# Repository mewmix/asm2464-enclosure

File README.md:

# ASM2464PD USB4 / M.2 2230 Development Enclosure

Open development project for a compact ASM2464PD + M.2 2230 USB4 enclosure with firmware-development access built into the board and enclosure.

The immediate goals are:

1. reproduce and then improve the public Leaves232 ASM2464PD 2230 reference design;
2. expose the ASM2464PD firmware UART cleanly;
3. provide safe direct SPI access to the external firmware flash for backup, programming, and recovery;
4. co-design the PCB and enclosure rather than treating the enclosure as an afterthought;
5. use an agent-driven KiCad workflow modeled on the public i2cjak Astra + KiStack + T3CAD demonstration;
6. validate as much of the digital/recovery path as possible in simulation before Rev-A hardware.

## Agent-driven workflow

The public i2cjak demonstration describes an Astra-Medium hardware-design loop using **KiStack** and **T3CAD**, a T3Code fork. The exact private prompt/transcript is not published, so this repository documents a reproducible workflow built from the public tools and their documented capabilities.

Start with [`WORKFLOW.md`](WORKFLOW.md). Agents working in this repository must also read [`AGENTS.md`](AGENTS.md) and [`PROJECT_PLAN.md`](PROJECT_PLAN.md).

## Reference design

Electrical/mechanical reference:

- https://github.com/Leaves232/2230-USB4-SSD-Enclosure-Design

Controller datasheet pointer and extracted debug pins:

- [`reference/datasheets/ASM2464PD.md`](reference/datasheets/ASM2464PD.md)

Known reference-board geometry already extracted from the public Gerber/PnP data:

- controller PCB: **22.039834 x 33.680400 mm**;
- ASM2464PD center: **(13.667257, 14.870481) mm** from the PCB lower-left datum;
- USB-C center: **(11.069980, 29.187267) mm**;
- M.2 connector center: **(11.023879, 4.697654) mm**.

## Firmware-development interface

The service interface is deliberately narrow:

- ASM UART TX/RX;
- ASM reset;
- direct external SPI flash CS#/CLK/DI/DO;
- GND and target-voltage sense.

See [`DEBUG_ACCESS_AGENT_INSTRUCTIONS.md`](DEBUG_ACCESS_AGENT_INSTRUCTIONS.md).

## Mechanical model

The current CadQuery fit model lives at:

```text
mechanical/rev-a/model.py
```

Build it with:

```bash
python -m venv .venv
source .venv/bin/activate
pip install -r mechanical/rev-a/requirements.txt
python mechanical/rev-a/model.py
```

Generated STEP/STL files belong under `mechanical/rev-a/build/` and are intentionally ignored until geometry is mature enough to publish as release artifacts.

## Integrated CAD / simulation milestone

The primary simulation target is now stock/reconstructed ASM behavior, pinned
to lifecycle commit `84c990c` with physical baseline `47aed2c`. The stock code
mode executes exact bounded helpers with boot ROM bypassed; full stock SPI
startup remains blocked. The 512 KiB stock flash profile is separate from the
2 MiB Rev-A design assumption. See [stock evidence and limits](validation/STOCK_GROUNDING.md).

The shared board configuration drives service access, SPI-isolation shunts,
flash envelope clearance and the virtual board. The secondary generic CPU
regression validates this project-owned diagnostic image's modeled UART/SPI,
brick and recovery behavior. It does not establish stock firmware or physical
silicon behavior. Existing CAD renders remain historical until regenerated.

```bash
python -m pip install -r simulation/requirements.txt
# Install SDCC using your platform package manager, then:
python scripts/validate_twin.py
```

See [validation outputs and limits](validation/README.md) and [the shared recovery design](hardware/rev-a/RECOVERY.md). STEP/STL and assembled/exploded PNGs are generated in `mechanical/rev-a/build/`. Geometry includes explicit provisional component envelopes, not a completed routed PCB.

**RTL remains blocked:** no Verilog/RTL sources exist at the inspected authoritative branch tip. `--require-rtl` makes that missing gate fail explicitly. No full dual-backend or fabrication-ready claim is made.

## Design gates before fabrication

Do not release Rev A for fabrication until:

- reference schematic/net tracing is complete;
- UART voltage is established;
- SPI flash voltage and exact part pinout are established;
- ASM SPI bus ownership under reset is proven or explicit isolation is designed;
- ERC/DRC pass with reviewed waivers only;
- USB4/PCIe routing rules are reviewed independently of generic DRC;
- debug connector and mating-cable keepouts are present in the mechanical model;
- ASM thermal path is modeled and does not depend on a printed-plastic lid for sustained operation;
- recovery simulation proves brick -> external flash recovery -> reboot -> UART confirmation.

## Source toolchain

- KiCad / `kicad-cli`
- KiStack: https://github.com/American-Embedded/KiStack
- T3CAD: https://github.com/i2cjak/T3CAD
- CadQuery
- Verilator + cocotb for digital board simulation
- ngspice/Xyce where circuit-level modeling is useful
- LiteNVMe as an optional open NVMe-host reference

## License / reference hygiene

Do not copy third-party source designs or datasheets into this repository unless their license permits redistribution. Keep source pointers, extracted facts, and our own derived design work separated and attributed.

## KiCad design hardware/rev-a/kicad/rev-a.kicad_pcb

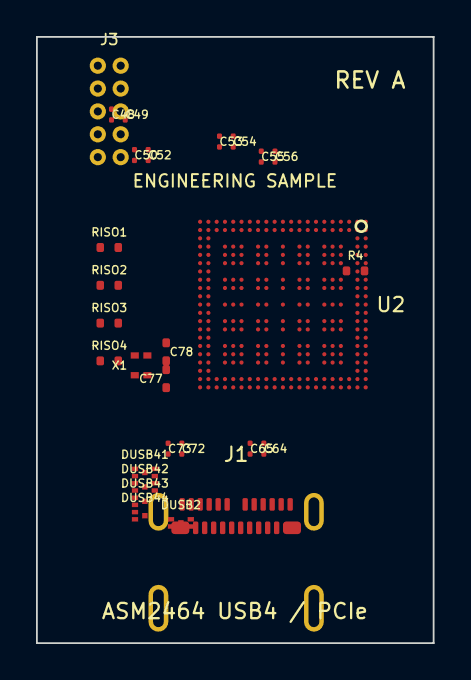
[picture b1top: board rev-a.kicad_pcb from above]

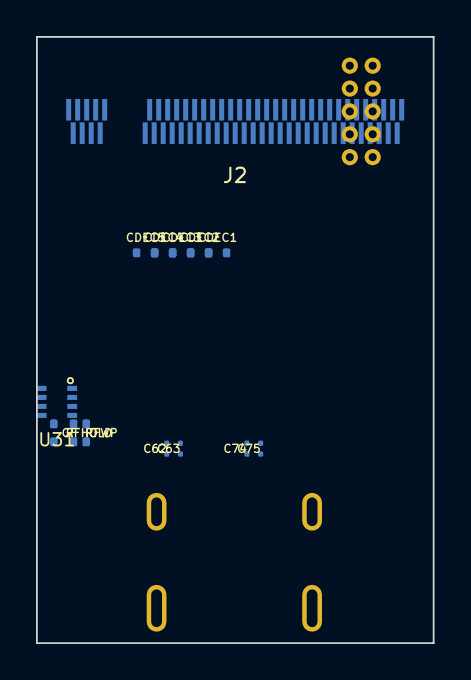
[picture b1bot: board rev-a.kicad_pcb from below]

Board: 2 copper layers, 22.0 x 33.7 mm, 42 parts (14 on the bottom side), 71 nets, no tracks yet.

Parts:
C48, C49, C50, C52, C53, C54, C55, C56, C64, C65, C74, C75: 220n; RevA_0201_2Pad
C62, C63, C72, C73: 330n; RevA_0201_2Pad
C77, C78: 30p; RevA_0402_2Pad
CDEC1, CDEC3, CDEC4, CDEC5: 100n; RevA_0402_2Pad
CDEC2: 2.2u; RevA_0402_2Pad
CF: 100n; RevA_0402_2Pad
DUSB2: ESD_2CH_SELECTION_PENDING; RevA_ESD2_SELECTION_PENDING_DUSB2
DUSB41: ESD_2CH_SELECTION_PENDING; RevA_ESD2_SELECTION_PENDING_DUSB41
DUSB42: ESD_2CH_SELECTION_PENDING; RevA_ESD2_SELECTION_PENDING_DUSB42
DUSB43: ESD_2CH_SELECTION_PENDING; RevA_ESD2_SELECTION_PENDING_DUSB43
DUSB44: ESD_2CH_SELECTION_PENDING; RevA_ESD2_SELECTION_PENDING_DUSB44
J1: 105450-0101; Molex_105450-0101
J2: APCI0113-P001A; LOTES_APCI0113-P001A_MKey_RECONSTRUCTED
J3: SERVICE_PROVISIONAL; RevA_Service_2x5_1.27_PROVISIONAL
R4: 12.1k; RevA_0402_2Pad
RFHOLD: 10k; RevA_0402_2Pad
RFWP: 10k; RevA_0402_2Pad
RISO1, RISO2, RISO3, RISO4: 0R_LINK; RevA_0402_2Pad
U2: ASM2464PD; ASM2464PD_BGA273_10x10_P0.46
U31: ZD25WQ16CEIGR; ZD25WQ16CEIGR_USON8_3x2_P0.5_RECONSTRUCTED
X1: 25MHz; RevA_Crystal_4P_1.6x1.2_X1

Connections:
+1V05: CDEC1.1, CDEC2.1, U2.D14, U2.D16, U2.E11, U2.E14, U2.E16, U2.F9, U2.F11, U2.F14, U2.F16, U2.H9, U2.H11, U2.H13, U2.H14, U2.H16, U2.J8, U2.J9, U2.J13, U2.J14, U2.J16, U2.J17, U2.J18, U2.J20, U2.J21, U2.K20, U2.K21, U2.L8, U2.L11, U2.L14, U2.N8, U2.N14, U2.P8, U2.P13, U2.P14, U2.T8, U2.T9, U2.T11, U2.T13, U2.T14, U2.U8, U2.U9
+1V8: CDEC3.1, U2.L6, U2.L16, U2.L17, U2.L18, U2.L20, U2.L21, U2.N6, U2.N16, U2.P6, U2.P16, U2.T6, U2.T16, U2.U6, U2.U11, U2.U13, U2.U14, U2.U16
+3V3: CDEC4.1, CF.1, J2.2, J2.4, J2.69, RFHOLD.2, RFWP.2, U2.D6, U2.D8, U2.D9, U2.D13, U2.E6, U2.E8, U2.E9, U2.E13, U2.F6, U2.F13, U2.H6, U31.8
+3V3A: CDEC5.1, U2.H5
ASM_REXT: R4.1, U2.AA3
ASM_RST_N: J3.5, U2.H1
ASM_SPI_CLK_CTRL: RISO2.1, U2.A5
ASM_SPI_CLK_FLASH: J3.7, RISO2.2, U31.6
ASM_SPI_CS_N_CTRL: RISO1.1, U2.A2
ASM_SPI_CS_N_FLASH: J3.6, RISO1.2, U31.1
ASM_SPI_DI_CTRL: RISO3.1, U2.A4
ASM_SPI_DI_FLASH: J3.8, RISO3.2, U31.2
ASM_SPI_DO_CTRL: RISO4.1, U2.A3
ASM_SPI_DO_FLASH: J3.9, RISO4.2, U31.5
ASM_UART_RX: J3.4, U2.A21
ASM_UART_TX: J3.3, U2.B21
ASM_XI: C77.1, U2.AA4, X1.1
ASM_XO: C78.1, U2.Y4, X1.3
FLASH_HOLD_N: RFHOLD.1, U31.7
FLASH_WP_N: RFWP.1, U31.3
GND: C77.2, C78.2, CDEC1.2, CDEC2.2, CDEC3.2, CDEC4.2, CDEC5.2, CF.2, DUSB2.5, DUSB41.5, DUSB42.5, DUSB43.5, DUSB44.5, J1.A1, J1.A12, J1.B1, J1.B12, J1.SH, J2.1, J2.3, J2.9, J2.15, J2.21, J2.27, J2.33, J2.39, J2.45, J2.51, J2.57, J2.67, J2.71, J2.73, J2.75, J3.1, J3.10, R4.2, U2.AA1, U2.AA2, U2.AA5, U2.AA9, U2.AA12, U2.AA14, U2.AA16, U2.AA18, U2.AA20, U2.AA21, U2.D4, U2.D5, U2.D11, U2.D17, U2.D18, U2.E4, U2.E5, U2.E17, U2.E18, U2.F4, U2.F5, U2.F8, U2.F17, U2.F18, U2.H4, U2.H8, U2.H17, U2.H18, U2.J4, U2.J5, U2.J6, U2.J11, U2.K2, U2.L1, U2.L2, U2.L4, U2.L5, U2.L9, U2.L13, U2.M20, U2.M21, U2.N1, U2.N2, U2.N4, U2.N5, U2.N9, U2.N11, U2.N13, U2.N17, U2.N18, U2.P4, U2.P5, U2.P9, U2.P11, U2.P17, U2.P18, U2.P20, U2.P21, U2.R1, U2.R2, U2.T4, U2.T5, U2.T17, U2.T18, U2.T20, U2.T21, U2.U1, U2.U2, U2.U4, U2.U5, U2.U17, U2.U18, U2.V4, U2.V5, U2.V6, U2.V8, U2.V9, U2.V11, U2.V13, U2.V14, U2.V16, U2.V17, U2.V18, U2.V20, U2.V21, U2.W1, U2.W2, U2.Y3, U2.Y5, U2.Y9, U2.Y12, U2.Y14, U2.Y16, U2.Y18, U2.Y20, U2.Y21, U31.4, X1.2, X1.4
PCIE_PERST_N: J2.50, U2.G21
PCIE_REFCLK_N: J2.53, U2.Y8
PCIE_REFCLK_P: J2.55, U2.AA8
PCIE_RX0_N_ASM: J2.41, U2.N20
PCIE_RX0_P_ASM: J2.43, U2.N21
PCIE_RX1_N_ASM: J2.29, U2.W20
PCIE_RX1_P_ASM: J2.31, U2.W21
PCIE_RX2_N_ASM: J2.17, U2.AA19
PCIE_RX2_P_ASM: J2.19, U2.Y19
PCIE_RX3_N_ASM: J2.5, U2.Y13
PCIE_RX3_P_ASM: J2.7, U2.AA13
PCIE_TX0_N_ASM: C55.1, U2.R21
PCIE_TX0_N_M2: C55.2, J2.47
PCIE_TX0_P_ASM: C56.1, U2.R20
PCIE_TX0_P_M2: C56.2, J2.49
PCIE_TX1_N_ASM: C53.1, U2.U21
PCIE_TX1_N_M2: C53.2, J2.35
PCIE_TX1_P_ASM: C54.1, U2.U20
PCIE_TX1_P_M2: C54.2, J2.37
PCIE_TX2_N_ASM: C50.1, U2.AA17
PCIE_TX2_N_M2: C50.2, J2.23
PCIE_TX2_P_ASM: C52.1, U2.Y17
PCIE_TX2_P_M2: C52.2, J2.25
PCIE_TX3_N_ASM: C48.1, U2.AA15
PCIE_TX3_N_M2: C48.2, J2.11
PCIE_TX3_P_ASM: C49.1, U2.Y15
PCIE_TX3_P_M2: C49.2, J2.13
USB2_DM: DUSB2.3, DUSB2.4, J1.A7, J1.B7, U2.M2
USB2_DP: DUSB2.1, DUSB2.2, J1.A6, J1.B6, U2.M1
USB4_URX0_N_ASM: C63.1, U2.P2
USB4_URX0_N_CONN: C63.2, DUSB43.3, DUSB43.4, J1.B10
USB4_URX0_P_ASM: C62.1, U2.P1
USB4_URX0_P_CONN: C62.2, DUSB43.1, DUSB43.2, J1.B11
USB4_URX1_N_ASM: C72.1, U2.Y1
USB4_URX1_N_CONN: C72.2, DUSB44.3, DUSB44.4, J1.A10
USB4_URX1_P_ASM: C73.1, U2.Y2
USB4_URX1_P_CONN: C73.2, DUSB44.1, DUSB44.2, J1.A11
USB4_UTX0_N_ASM: C65.1, U2.T2
USB4_UTX0_N_CONN: C65.2, DUSB41.3, DUSB41.4, J1.A3
USB4_UTX0_P_ASM: C64.1, U2.T1
USB4_UTX0_P_CONN: C64.2, DUSB41.1, DUSB41.2, J1.A2
USB4_UTX1_N_ASM: C74.1, U2.V1
USB4_UTX1_N_CONN: C74.2, DUSB42.3, DUSB42.4, J1.B3
USB4_UTX1_P_ASM: C75.1, U2.V2
USB4_UTX1_P_CONN: C75.2, DUSB42.1, DUSB42.2, J1.B2
USB_CC1: J1.A5, U2.AA6
USB_CC2: J1.B5, U2.Y6
USB_SBU1: J1.A8, U2.K1
USB_SBU2: J1.B8, U2.J1
VBUS_5V: J1.A4, J1.A9, J1.B4, J1.B9

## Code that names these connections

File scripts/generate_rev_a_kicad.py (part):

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    "GND", "+3V3", "+3V3A", "+1V8", "+1V05", "VBUS_5V", "VBUS_5V_SENSE", "VREF_SENSE",
    "USB_CC1", "USB_CC2", "USB_SBU1", "USB_SBU2", "USB2_DP", "USB2_DM",
    "ASM_RST_N", "ASM_UART_TX", "ASM_UART_RX", "ASM_TEST_EN", "ASM_I2C_DATA", "ASM_I2C_CLK",
    "ASM_GPIO0", "ASM_GPIO1", "ASM_GPIO2", "ASM_GPIO3", "ASM_GPIO8_CLKREQ_N", "ASM_GPIO14", "ASM_HDDPC", "ASM_REXT", "ASM_XI", "ASM_XO",
    "ASM_SPI_CS_N_CTRL", "ASM_SPI_CLK_CTRL", "ASM_SPI_DI_CTRL", "ASM_SPI_DO_CTRL",
    "ASM_SPI_CS_N_FLASH", "ASM_SPI_CLK_FLASH", "ASM_SPI_DI_FLASH", "ASM_SPI_DO_FLASH",
    "FLASH_WP_N", "FLASH_HOLD_N",
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    else: out += fp_texts()
    fab="B.Fab" if instance else "F.Fab"; crt="B.CrtYd" if instance else "F.CrtYd"
    out += rect_lines(-1,-1.5,1,1.5,fab,0.1); out += rect_lines(-1.25,-1.75,1.25,1.75,crt,0.05)
    pin_nets={1:"ASM_SPI_CS_N_FLASH",2:"ASM_SPI_DI_FLASH",3:"FLASH_WP_N",4:"GND",5:"ASM_SPI_DO_FLASH",6:"ASM_SPI_CLK_FLASH",7:"FLASH_HOLD_N",8:"+3V3"}
    # Four pads on each long side; exposed thermal/ground pad as EP.
    ys=[-0.75,-0.25,0.25,0.75]
    for i,y in enumerate(ys,1):
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    u2_pins=[(b,BALL_NET[b],"bidirectional") for b in u2_nums]
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    j2_pins=[(pn,net,"bidirectional") for pn,net in j2_map.items()]
    u31_pins=[("1","ASM_SPI_CS_N_FLASH","input"),("2","ASM_SPI_DI_FLASH","output"),("3","FLASH_WP_N","input"),("4","GND","power_in"),("5","ASM_SPI_DO_FLASH","input"),("6","ASM_SPI_CLK_FLASH","input"),("7","FLASH_HOLD_N","input"),("8","+3V3","power_in")]
    j3_names=["GND","VREF_SENSE","ASM_UART_TX","ASM_UART_RX","ASM_RST_N","ASM_SPI_CS_N_FLASH","ASM_SPI_CLK_FLASH","ASM_SPI_DI_FLASH","ASM_SPI_DO_FLASH","GND"]
    j3_pins=[(str(i+1),n,"bidirectional") for i,n in enumerate(j3_names)]

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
